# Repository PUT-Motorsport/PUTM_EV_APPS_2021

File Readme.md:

# Accelerator Pedal Position Sensor (APPS)

## Motivation

APPS handling is required by official FSG Rules according to T11.8 ([see](https://www.formulastudent.de/fileadmin/user_upload/all/2022/rules/FS-Rules_2022_v1.0.pdf#page=58)). APPS signals are system critical signals meaning that any implausibility between sensors or a failure should result in complete motor power shutdown.

## Pedal travel

* 0% - fully released
* 100% - fully applied

## Implausiblity

Implausibility is defined as a deviation of more than ten percentage points pedal travel
between any of the used APPSs. If it occurs for more than 100 ms the power to the motor must be immediately shut down.

## Platform

Software for APPS signal handling is developed using C++ for STM32 microcontroller.

## Program schematic

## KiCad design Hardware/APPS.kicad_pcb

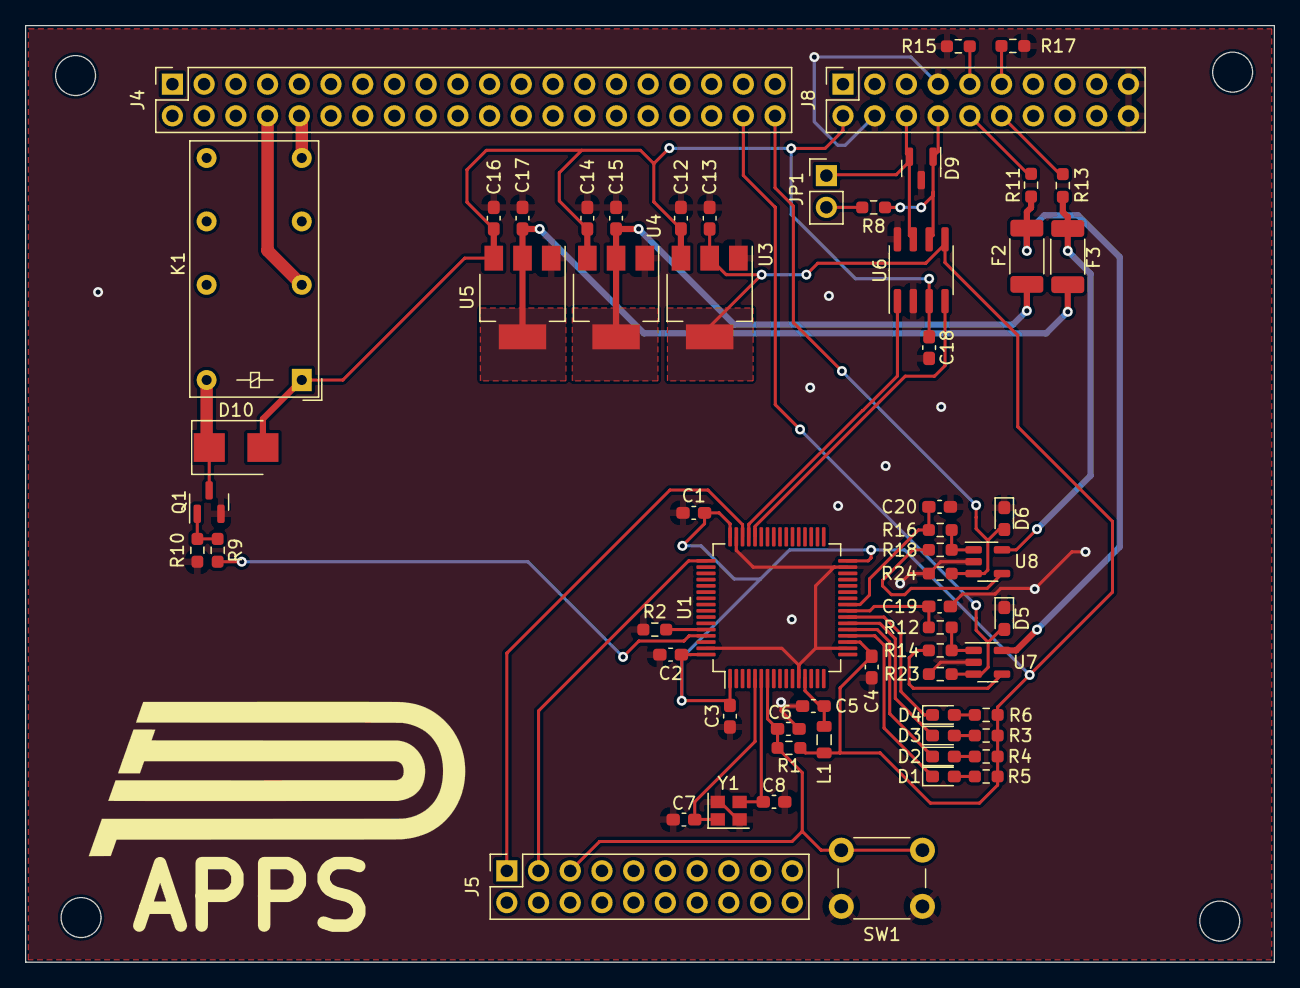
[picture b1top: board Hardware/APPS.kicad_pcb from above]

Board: 2 copper layers, 100.0 x 75.0 mm, 62 parts (0 on the bottom side), 44 nets.

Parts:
C1, C2, C3, C4, C5, C6, C12, C13, C14, C15, C16, C17, C18: 100nF; C_0603_1608Metric_Pad1.08x0.95mm_HandSolder
C7, C8: 22pF; C_0603_1608Metric_Pad1.08x0.95mm_HandSolder
C19, C20: 100n; C_0603_1608Metric_Pad1.08x0.95mm_HandSolder
D1, D2, D3, D4: LED; LED_0603_1608Metric_Pad1.05x0.95mm_HandSolder
D5, D6: D_TVS; D_0603_1608Metric_Pad1.05x0.95mm_HandSolder
D9: PESD2CAN.215; SOT-23
D10: DIODE; D_SMB
F2, F3: Fuse; Fuse_2010_5025Metric
J4: Sygnały; PinSocket_2x20_P2.54mm_Vertical
J5: Diagnostyka; PinSocket_2x10_P2.54mm_Vertical
J8: Zasilanie+CAN; PinSocket_2x10_P2.54mm_Vertical
JP1: Jumper_NC_Small; PinHeader_1x02_P2.54mm_Vertical
K1: FINDER-30.22; Relay_DPDT_Finder_30.22
L1: 10u; L_0805_2012Metric
Q1: BSS138; SOT-23
R1, R2, R10: 10k; R_0603_1608Metric_Pad0.98x0.95mm_HandSolder
R3, R4, R5, R6: 300R; R_0603_1608Metric_Pad0.98x0.95mm_HandSolder
R8: 120R; R_0603_1608Metric_Pad0.98x0.95mm_HandSolder
R9: 100R; R_0603_1608Metric_Pad0.98x0.95mm_HandSolder
R11, R17: 220R; R_0603_1608Metric_Pad0.98x0.95mm_HandSolder
R12, R16: 4k7; R_0603_1608Metric_Pad0.98x0.95mm_HandSolder
R13, R14, R15, R18: 0R; R_0603_1608Metric_Pad0.98x0.95mm_HandSolder
R23, R24: 100k; R_0603_1608Metric_Pad0.98x0.95mm_HandSolder
SW1: SW_Push; SW_PUSH_6mm
U1: STM32L4P5RET6; LQFP-64_10x10mm_P0.5mm
U3, U4, U5: LM1117-3.3; SOT-223-3_TabPin2
U6: MCP2562-H-SN; SOIC-8_3.9x4.9mm_P1.27mm
U7, U8: MCP6001-OT; SOT-23-5
Y1: Crystal_GND24; Crystal_SMD_2520-4Pin_2.5x2.0mm

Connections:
3V3_POT1: F2.1, R11.1, U7.5 (V+)
3V3_POT2: F3.1, R13.1, U8.5 (V+)
+5V: C12.1, C14.1, C16.1, C18.1, D10.2 (A), J8.2, K1.A1, U3.3 (VI), U4.3 (VI), U5.3 (VI), U6.3 (VDD)
/3V3_A: C5.1, L1.2, U1.13 (VDDA/VREF+)
/3V3_SYS: C1.1, C2.1, C3.1, C4.1, C13.1, L1.1, R1.2, R3.2, R4.2, R5.1, R6.1, U1.1 (VBAT), U1.19 (VDD), U1.32 (VDD), U1.48 (VDDUSB), U1.64 (VDD), U3.2 (VO), U6.5 (Vio)
/CAN-RX: U1.44 (PA11), U6.4 (RXD)
/CAN-TX: U1.45 (PA12), U6.1 (TXD)
/EN_RELAY: R9.2, U1.61 (PB8)
/LED1: D1.1 (K), U1.20 (PA4)
/LED2: D2.1 (K), U1.21 (PA5)
/LED3: D3.1 (K), U1.22 (PA6)
/LED4: D4.1 (K), U1.23 (PA7)
/PowerModule/VO_POT1: C15.1, F2.2, U4.2 (VO)
/PowerModule/VO_POT2: C17.1, F3.2, U5.2 (VO)
/SENSOR1: C19.1, R12.1, U1.24 (PC4)
/SENSOR2: C20.1, R16.1, U1.25 (PC5)
/XTAL1: C7.1, U1.5 (PH0-OSC_IN), Y1.1
/XTAL2: C8.1, U1.6 (PH1-OSC_OUT), Y1.3
CAN-H: D9.2 (A2), J8.6, JP1.1, U6.7 (CANH)
CAN-L: D9.1 (A1), J8.8, R8.2, U6.6 (CANL)
CLK: J5.3, U1.49 (PA14)
GND: C1.2, C2.2, C3.2, C4.2, C5.2, C6.2, C7.2, C8.2, C12.2, C13.2, C14.2, C15.2, C16.2, C17.2, C18.2, C19.2, C20.2, D5.1 (A1), D6.1 (A1), D9.3 (common), J8.4, J8.7, J8.19, J8.20, Q1.2 (S), R2.1, R10.2, R15.1, R17.1, R23.2, R24.2, SW1.1, U1.12 (VSSA/VREF-), U1.18 (VSS), U1.31 (VSS), U1.47 (VSS), U1.63 (VSS), U3.1 (GND), U4.1 (GND), U5.1 (GND), U6.2 (VSS), U6.8 (STBY), U7.2 (V-), U8.2 (V-), Y1.2, Y1.4
NRST: C6.1, J5.5, R1.1, SW1.2, U1.7 (NRST)
unnamed: D1.2 (A), R5.2
unnamed: D2.2 (A), R4.1
unnamed: D3.2 (A), R3.1
unnamed: D4.2 (A), R6.2
unnamed: D10.1 (K), K1.A2, Q1.3 (D)
unnamed: J8.9, R15.2
unnamed: J8.10, R11.2
unnamed: J8.11, R17.2
unnamed: J8.12, R13.2
unnamed: JP1.2, R8.1
unnamed: Q1.1 (G), R9.1, R10.1
unnamed: R2.2, U1.60 (PH3-BOOT)
unnamed: R12.2, R14.1, U7.1
unnamed: R14.2, U7.4 (-)
unnamed: R16.2, R18.1, U8.1
unnamed: R18.2, U8.4 (-)
SAFETY-IN: J4.8, K1.11
SAFETY-OUT: J4.10, K1.14
SIG_APPS1: D5.2 (A2), J4.38, R23.1, U7.3 (+)
SIG_APPS2: D6.2 (A2), J4.40, R24.1, U8.3 (+)
SWD: J5.1, U1.46 (PA13)

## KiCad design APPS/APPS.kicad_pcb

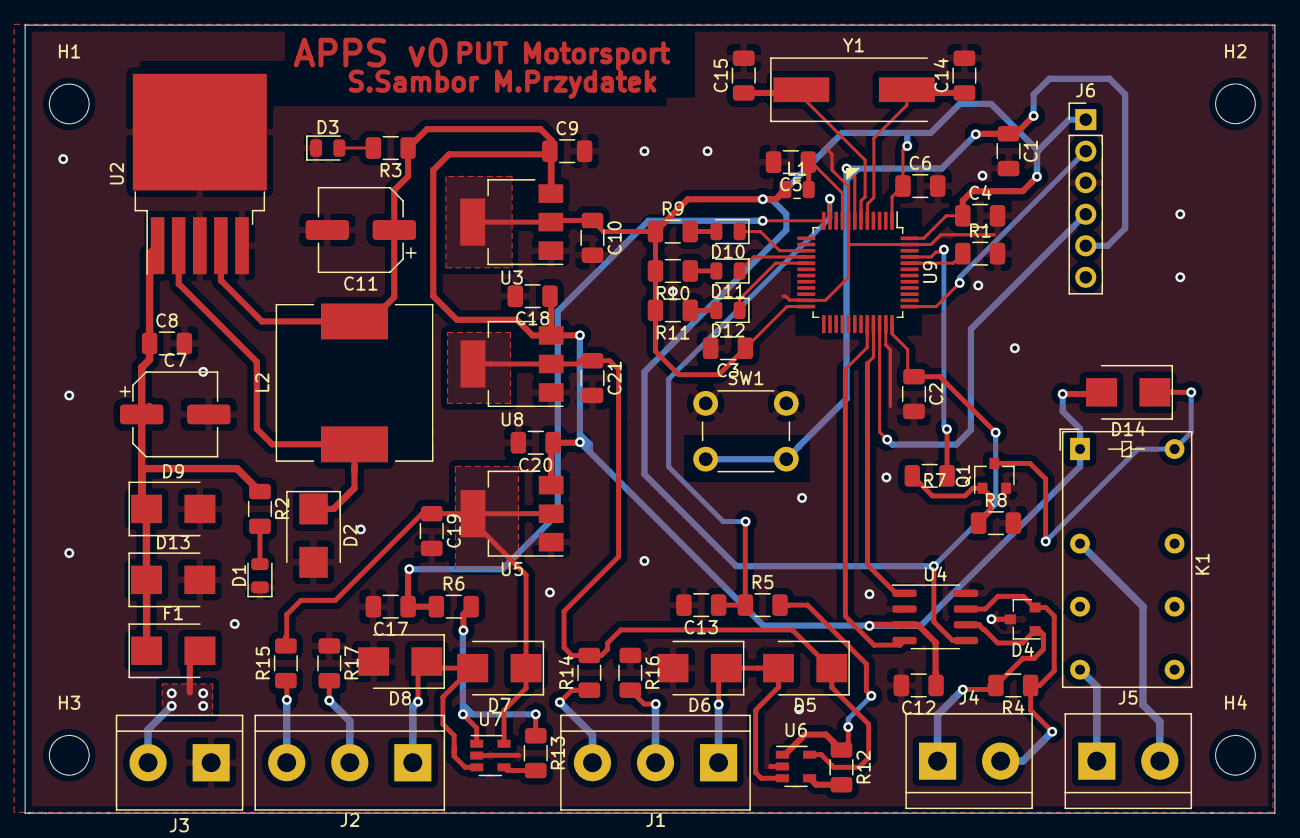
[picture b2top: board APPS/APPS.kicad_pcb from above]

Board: 2 copper layers, 100.7 x 63.5 mm, 76 parts (0 on the bottom side), 44 nets.

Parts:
C1, C2, C3, C4, C5, C6, C8, C9, C10, C12, C18, C19, C20, C21: 100nF; C_1206_3216Metric
C7: 100u; CP_Elec_6.3x7.7
C11: 220u; CP_Elec_6.3x7.7
C13, C17: 1uF; C_1206_3216Metric
C14, C15: 22pF; C_1206_3216Metric
D1, D3, D10, D11, D12: LED; LED_0805_2012Metric
D2, D5, D6, D7, D8, D13: D_Schottky; D_SMB
D4: PESD2CAN.215; SOT-23
D9: D_Zener; D_SMB
D14: DIODE; D_SMB
F1: Polyfuse; D_SMB
H1, H2, H3, H4: MountingHole; MountingHole_3.2mm_M3
J1, J2: Screw_Terminal_01x03; TerminalBlock_bornier-3_P5.08mm
J3, J4, J5: Screw_Terminal_01x02; TerminalBlock_bornier-2_P5.08mm
J6: Conn_01x06_Male; PinHeader_1x06_P2.54mm_Vertical
K1: FINDER-30.22; Relay_DPDT_Finder_30.22
L1: L; L_0805_2012Metric
L2: 33u; L_12x12mm_H8mm
Q1: BSS138; SOT-23
R1: R_Small; R_1206_3216Metric
R2, R3, R9, R10, R11: R; R_1206_3216Metric
R4: 120R; R_1206_3216Metric
R5, R6, R12, R13: 300R; R_1206_3216Metric
R7: 100R; R_1206_3216Metric
R8: 10k; R_1206_3216Metric
R14, R15, R16, R17: 0R; R_1206_3216Metric
SW1: SW_Push; SW_PUSH_6mm
U2: LM2596S-5; TO-263-5_TabPin3
U3, U5, U8: LM1117-3.3; SOT-223-3_TabPin2
U4: MCP2562-H-SN; SOIC-8_3.9x4.9mm_P1.27mm
U6, U7: MCP6001-OT; SOT-23-5
U9: STM32F103C8Tx; LQFP-48_7x7mm_P0.5mm
Y1: Crystal 8 MHz; Crystal_SMD_HC49-SD

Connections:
+3.3VA: C21.1, D5.1, R14.2, U6.5, U8.2
+3.3VADC: C19.1, D7.1, R15.2, U5.2, U7.5
+5V: C9.1, C11.1, C12.1, C18.1, C20.1, D14.2, K1.A1, L2.2, R3.1, U2.4, U3.3, U4.3, U5.3, U8.3
+12V: C7.1, C8.1, D9.1, D13.1, F1.1, R2.1, U2.1
Ain0: C13.1, R5.1, U9.11
Ain1: C17.1, R6.1, U9.12
CAN_H: D4.2, J4.2, R4.1, U4.7
CAN_L: D4.1, J4.1, R4.2, U4.6
CAN_RX: U4.4, U9.32
CAN_TX: U4.1, U9.33
EN_RELAY: R7.2, U9.45
NRST: C1.1, J6.5, SW1.2, U9.7
unnamed: C5.1, L1.2, U9.9
unnamed: C14.1, U9.5, Y1.2
unnamed: C15.1, U9.6, Y1.1
unnamed: D1.2, R2.2
unnamed: D2.1, L2.1, U2.2
unnamed: D3.2, R3.2
unnamed: D5.2, D6.1, J1.1, U6.3
unnamed: D7.2, D8.1, J2.1, U7.3
unnamed: D10.1, U9.15
unnamed: D10.2, R9.2
unnamed: D11.1, U9.16
unnamed: D11.2, R10.1
unnamed: D12.1, U9.17
unnamed: D12.2, R11.1
unnamed: D14.1, K1.A2, Q1.3
unnamed: F1.2, J3.2
unnamed: J1.2, R16.2
unnamed: J1.3, R14.1
unnamed: J2.2, R17.2
unnamed: J2.3, R15.1
unnamed: Q1.1, R7.1, R8.1
unnamed: R1.1, U9.44
unnamed: R5.2, R12.1, U6.1
unnamed: R12.2, U6.4
unnamed: R6.2, R13.1, U7.1
unnamed: R13.2, U7.4
SAFETY1: J5.1, K1.14
SAFETY2: J5.2, K1.11
SWCLK: J6.2, U9.37
SWDIO: J6.4, U9.34
SW_GND: C1.2, C2.2, C3.2, C4.2, C5.2, C6.2, C7.2, C8.2, C9.2, C10.2, C11.2, C12.2, C13.2, C14.2, C15.2, C17.2, C18.2, C19.2, C20.2, C21.2, D1.1, D2.2, D3.1, D4.3, D6.2, D8.2, D9.2, D13.2, J3.1, J6.3, Q1.2, R1.2, R8.2, R16.1, R17.1, SW1.1, U2.3, U2.5, U3.1, U4.2, U4.8, U5.1, U6.2, U7.2, U8.1, U9.8, U9.23, U9.35, U9.47
SW_VDDtarget: C2.1, C3.1, C4.1, C6.1, C10.1, J6.1, L1.1, R9.1, R10.2, R11.2, U3.2, U4.5, U9.1, U9.24, U9.36, U9.48

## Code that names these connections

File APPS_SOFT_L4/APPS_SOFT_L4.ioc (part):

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Mcu.UserName=STM32L4P5RETx
PH0-OSC_IN\ (PH0).Signal=RCC_OSC_IN
PA12.GPIOParameters=GPIO_Label
PA11.GPIOParameters=GPIO_Label
PA11.Mode=CAN_Activate
PA6.GPIO_Label=LED_2
RCC.SYSCLKSource=RCC_SYSCLKSOURCE_PLLCLK
PA14\ (JTCK/SWCLK).Signal=SYS_JTCK-SWCLK
PA12.Signal=CAN1_TX
PH1-OSC_OUT\ (PH1).Mode=HSE-External-Oscillator
RCC.HSE_VALUE=16000000
PC4.GPIO_Label=ADC1_IN1
PA0.Mode=Asynchronous
PA14\ (JTCK/SWCLK).Mode=Serial_Wire
PA0.Signal=UART4_TX
Mcu.Package=LQFP64
PA6.Signal=GPIO_Output
PA5.GPIOParameters=GPIO_Label
PC5.Signal=ADCx_IN14
PH0-OSC_IN\ (PH0).Mode=HSE-External-Oscillator
PC4.GPIOParameters=GPIO_Label
PA6.GPIOParameters=GPIO_Label
PB8.GPIOParameters=GPIO_Label
PA13\ (JTMS/SWDIO).Mode=Serial_Wire
PC4.Signal=ADCx_IN13
PA11.GPIO_Label=CAN_RX
PA12.GPIO_Label=CAN_TX
PH1-OSC_OUT\ (PH1).Signal=RCC_OSC_OUT
PB8.GPIO_Label=SAFETY
PB4\ (NJTRST).GPIOParameters=GPIO_Label
PC5.GPIOParameters=GPIO_Label
PA1.Signal=UART4_RX
PA5.Signal=GPIO_Output
board=custom
PA1.Mode=Asynchronous
Mcu.Name=STM32L4P5R(G-E)Tx
RCC.SYSCLKFreq_VALUE=32000000
PA7.GPIO_Label=LED_3
PA12.Mode=CAN_Activate
PA5.GPIO_Label=LED_1
PC5.GPIO_Label=ADC2_IN2
PA11.Signal=CAN1_RX
PB8.Signal=GPIO_Output
PB4\ (NJTRST).GPIO_Label=BT_LED
PA7.GPIOParameters=GPIO_Label
PA13\ (JTMS/SWDIO).Signal=SYS_JTMS-SWDIO
PA7.Signal=GPIO_Output
PB4\ (NJTRST).Signal=GPIO_Output

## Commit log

2020-12-06 init commit with soft- and hard-ware
2020-12-06 CAN 500, should not work
2020-12-08 check analog input if it is correctly calibrated
2021-03-19 updated timers
2021-04-21 gitignore
2021-04-21 Added files from remote work
2021-04-21 Changed PCB edhes shape
2021-04-21 Deleted mounting holes from schematic (now on pcb edgecuts)
2021-04-22 Positioned Bluetooth module
2021-04-22 Updated BT position
2021-04-27 Changed HC-05 pins for other Forbot HC-05
2021-04-27 Quick fixes
2021-04-27 handling error - difference beetween sensors is too big
2021-04-27 Added sensors' error handler If difference is too big it should be measurement should be 0
2021-04-29 New boundaries, error handlers
2021-05-06 Updated buttons position
2021-05-06 Updated graph
2021-05-06 Removed redundant variables
2021-05-07 Added controll of delay with one byte number
2021-05-07 Arduino code for debugging Android Studio App
2021-05-07 Changed folder structure
2021-05-07 Updated time dependent graph
2021-05-07 Adjusted sampling frequency scale
2021-05-07 Adjusted GraphView
2021-05-07 Added PUT Motorsport Icon (All possible formats)
2021-05-07 Adjusted layout
2021-05-10 PCB router 50%
2021-05-10 Components labels placed
2021-05-10 Added Logos library, PCB FINISHED
2021-05-17 Dadded second graph series
2021-05-18 Max CSV file length set to 5 min
2021-05-19 GitIgnore update
2021-06-20 cleaned
2021-06-20 rewritten for L4
2021-09-17 cpp and whole code refactor
2021-09-17 calibration min/max values on PM07
2021-09-20 fix 5% dead zone to comply with 2020 rules
2021-12-19 Calibration values for Dyno 16.12.2021
2022-01-07 Changed footprints and PCB layout. Schematic cleanup.
2022-01-07 Schematic cleanup and description
2022-01-07 PCB layout and routing
2022-01-10 Deleted 24V section
2022-01-13 Changed crystal footprint, fixed capactiors, added debug LED
2022-01-13 Fixed CAN lines to be equal length
2022-01-13 Schematic cleanup
2022-01-14 Generated BOM
2022-01-19 Switch STM capacitors' positions, added mounting
2022-02-28 Added readme.
